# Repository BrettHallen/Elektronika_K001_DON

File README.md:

# Электроника К 001 ДОН<br>Elektronika K 001 DON
Information about the Specialist-compatible constructor kit computer manufactured in Rostov-on-Don (Ростов-на-Дону) in the Russian SFSR by [ПАО "ГРАНИТ" (Granite)](https://www.paogranit.ru/) in the late 1980s.

Here is the packaging - the poly is quite dense and in very good condition, but the label has degraded somewhat I'm afraid.<br>

The blurb on the top of the box says the following:<br>
> Набор "Конструктор" Персональной микро-ЭВМ<br>
>
> Набор-конструктор микро-ЭВМ:<br>
> 1. Для сборки микро-ЭВМ;
> 2. Для ознакомления с устройством микро-ЭВМ;
> 3. Для ознакомления с основами компьютерной техники.<br>
>
> Собранная микро-ЭВМ:
> 1. Обучает по разным общеобразовательным и специальным программам;
> 2. Решает задачи в режиме программируемого калькулятора;
> 3. Реализует разнообразные программы интеллектуальных игр;
> 4. Хранит составленный Вами банк данных.

In English:<br>
> Kit "Constructor" Personal Microcomputer<br>
>
> Microcomputer Constructor Kit:<br>
> 1. For assembling a microcomputer;
> 2. For familiarising yourself with the structure of a microcomputer;
> 3. For familiarising yourself with the basics of computer technology.
>
> Assembled microcomputer:
> 1. Provides training using various general education and specialised programs;
> 2. Solves problems in programmable calculator mode;
> 3. Runs a variety of intellectual game programs;
> 4. Stores the database you have created.

## Videos
- [Part 1: Initial Look](https://youtu.be/PEJ6cLXKCgM)
- [Part 2: First Power On](https://youtu.be/MBkoUaQZSSI)
- [Part 3: Video Fault](https://youtu.be/eovsz4YsJxw)

## Firmware
A dump of the КС573РФ2 (2716 analogue) EPROM.<br>

This has some minor differences with the original C000 Loader binary for the [Specialist](/Specialist_Information/Firmware).<br>

## Video Output
It has a 5-pin DIN for audio & video output:<br>
- Pin 1 = audio
- Pin 2 = ground
- Pin 3 = n/c
- Pin 4 = video (B&W)
- Pin 5 = n/c

## [Power](/Elektronika_K001_DON_Power)
This appears to be the pinout for the 5-pin DIN power socket:
- Pin 1 = +12V regulated
- Pin 2 = ground (общий)
- Pin 3 = +5V regulated
- Pin 4 = -5V unregulated
- Pin 5 = -5V unregulated

I have created a simple replacement that uses a regulated +12VDC power supply and generates regulated ±5V output.<br>

## [Replacement Keyboard](/Elektronika_K001_DON_Keyboard)
The keyboard is a pretty neat design for the time, nice & simple.  Luckily it is quite easy to replace so here is my attempt using Cherry MX key switches.<br>

Interestingly the Specialist design has a row of function keys along the top: HELP, EDIT, RUN, etc.<br>

These aren't labelled on the K001 DON but they should function - I have included them.<br>

### Special Keys
There are some Soviet-specific keys on the keyboard - here is my rough understanding:
- НР = Нижний Регистр (lower case/register)
- НР ФИКС = Нижний Регистр Fix (shift lock)
- ЗБ = Забой (backspace)
- ПС = Перевод Строки (line feed)
- ПВ = Повтор/Вставка (auto-repeat)
- ВК = Возврат Каретки (carriage return)
- СБР = Сброс (reset)

## Useful Links
### [Alexey's Vintage Sovit Computer Repository](/Specialist_Information)
A great source of information about the Specialist design can be found on [Alexey's retro computer repository](https://github.com/alemorf/retro_computers).<br>

I have copied some of the useful information such as the original firmware and "Modelist Constructor" magazine articles.<br>

### [Mick Laboratory](http://www.micklab.ru/Specialist.htm)

### [spetsialist-mx.ru](https://web.archive.org/web/20210722200656/http://www.spetsialist-mx.ru/)
Unfortunately the original site is lost so there is only this archive.  I have added some of the useful info to the Specialist section here as an additional backup - this included a [scan of the DON's manual](https://web.archive.org/web/20210516222216/http://spetsialist-mx.ru/index16.html)!

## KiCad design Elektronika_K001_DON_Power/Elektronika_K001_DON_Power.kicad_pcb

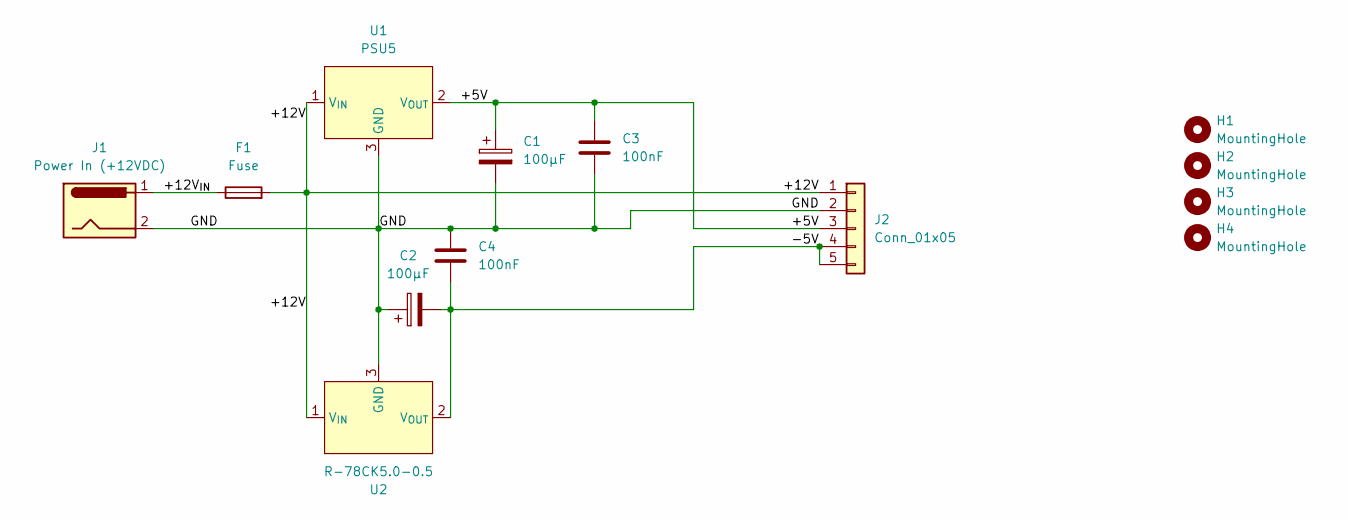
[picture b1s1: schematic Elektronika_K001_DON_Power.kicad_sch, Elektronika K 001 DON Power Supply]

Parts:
C1, C2: 100µF; CP_Radial_D6.3mm_P2.50mm
C3, C4: 100nF; C_Disc_D3.8mm_W2.6mm_P2.50mm
F1: Fuse; Fuseholder_Clip-5x20mm_Littelfuse_111_Inline_P20.00x5.00mm_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
H1, H2, H3, H4: MountingHole; MountingHole_3.2mm_M3_DIN965
J1: Power In (+12VDC); BarrelJack_CUI_PJ-063AH_Horizontal
J2: Conn_01x05; 6710601
U1: PSU5; TO-3
U2: R-78CK5.0-0.5; TO-220-3_Vertical; Manufacturer_Part_Number R-78CK5.0-0.5

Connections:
/+5V: C1.1, C3.1, J2.3, U1.2 (V_{OUT})
/+12V: F1.2, J2.1, U1.1 (V_{IN}), U2.1 (V_{IN})
/+12V_{IN}: F1.1, J1.1
/-5V: C2.2, C4.1, J2.4, J2.5, U2.2 (V_{OUT})
/GND: C1.2, C2.1, C3.2, C4.2, J1.2, J2.2, U1.3 (GND), U2.3 (GND)

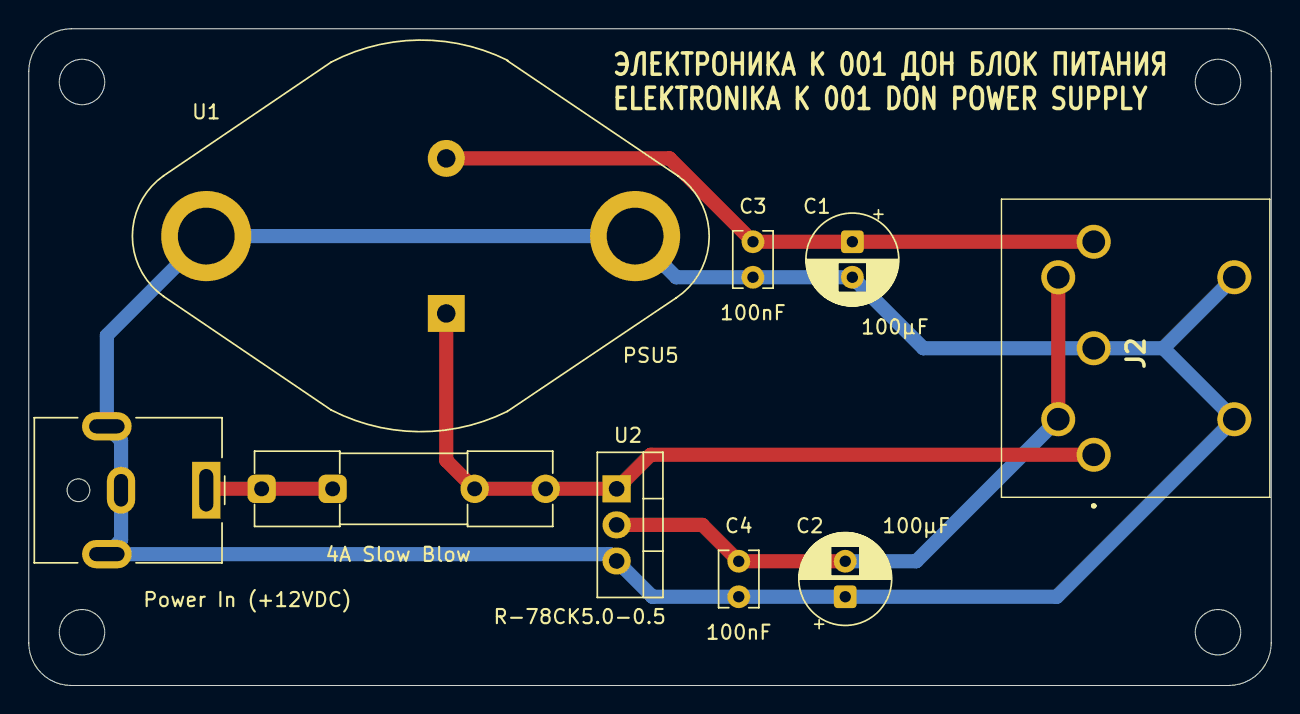
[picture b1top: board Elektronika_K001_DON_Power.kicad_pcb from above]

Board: 2 copper layers, 87.5 x 46.2 mm, 13 parts (0 on the bottom side), 5 nets.

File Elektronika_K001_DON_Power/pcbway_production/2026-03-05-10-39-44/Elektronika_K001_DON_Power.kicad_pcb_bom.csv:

Designator,Quantity,Value,Footprint,Package,MPN,DNP,Mount_Type,Description,Height,Manufacturer_Name
"C1, C2",2,100µF,CP_Radial_D6.3mm_P2.50mm,,,,tht,Polarized capacitor,,
"C3, C4",2,100nF,C_Disc_D3.8mm_W2.6mm_P2.50mm,,,,tht,Unpolarized capacitor,,
J1,1,Power In (+12VDC),BarrelJack_CUI_PJ-063AH_Horizontal,,,,tht,DC Barrel Jack,,
J2,1,Conn_01x05,6710601,,,,tht,"Generic connector, single row, 01x05, script generated (kicad-library-utils/schlib/autogen/connector/)",,
U1,1,PSU5,TO-3,,,,tht,,,
U2,1,R-78CK5.0-0.5,TO-220-3_Vertical,,R-78CK5.0-0.5,,tht,0.5A DC/DC-Converter \'INNOLINE\' SIP3 reg,10.7,RECOM Power

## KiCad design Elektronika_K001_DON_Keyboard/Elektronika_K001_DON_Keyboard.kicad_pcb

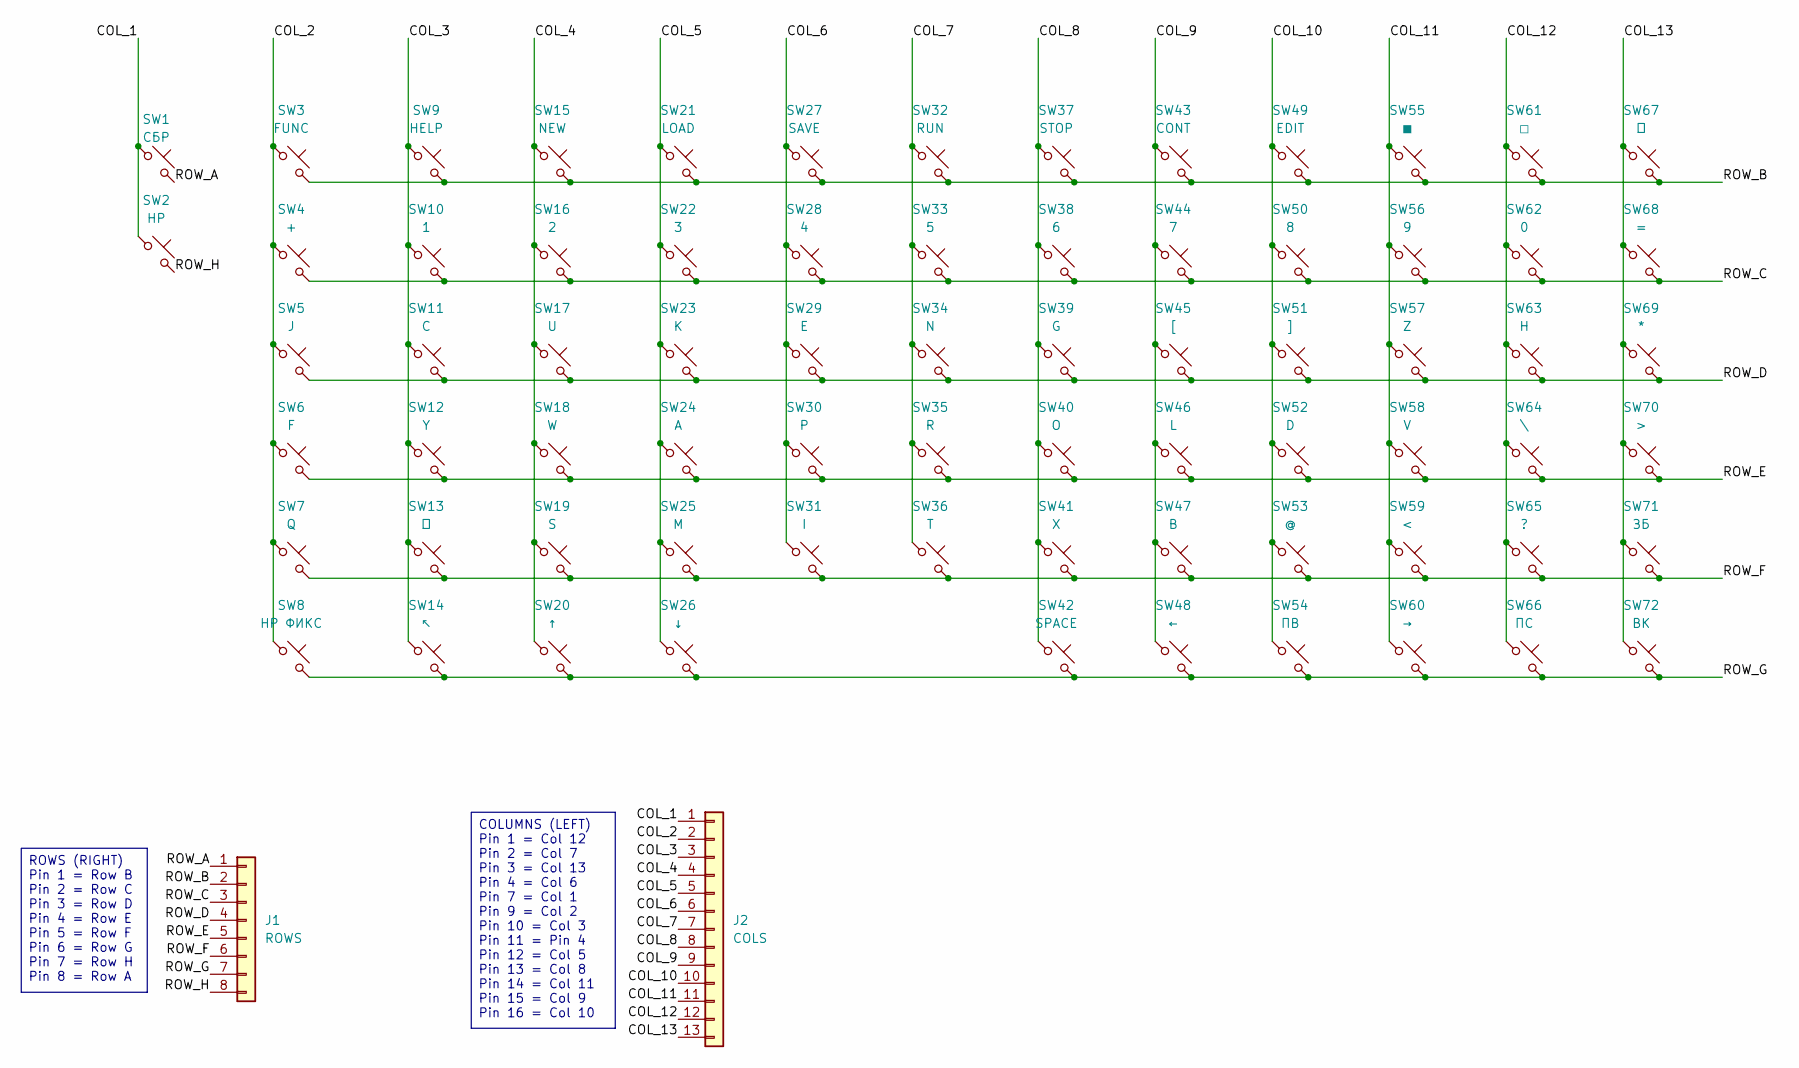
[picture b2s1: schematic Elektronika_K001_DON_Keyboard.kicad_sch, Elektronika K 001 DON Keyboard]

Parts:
J1: ROWS; PinHeader_1x08_P2.54mm_Vertical
J2: COLS; PinHeader_1x13_P2.54mm_Vertical
SW1: СБР; SW_Gateron_LowProfile_THT
SW2: НР; SW_Gateron_LowProfile_THT
SW3: FUNC; SW_Gateron_LowProfile_THT
SW4: +; SW_Gateron_LowProfile_THT
SW5: J; SW_Gateron_LowProfile_THT
SW6: F; SW_Gateron_LowProfile_THT
SW7: Q; SW_Gateron_LowProfile_THT
SW8: НР ФИКС; SW_Gateron_LowProfile_THT
SW9: HELP; SW_Gateron_LowProfile_THT
SW10: 1; SW_Gateron_LowProfile_THT
SW11: C; SW_Gateron_LowProfile_THT
SW12: Y; SW_Gateron_LowProfile_THT
SW13: ⎴; SW_Gateron_LowProfile_THT
SW14: ↖; SW_Gateron_LowProfile_THT
SW15: NEW; SW_Gateron_LowProfile_THT
SW16: 2; SW_Gateron_LowProfile_THT
SW17: U; SW_Gateron_LowProfile_THT
SW18: W; SW_Gateron_LowProfile_THT
SW19: S; SW_Gateron_LowProfile_THT
SW20: ↑; SW_Gateron_LowProfile_THT
SW21: LOAD; SW_Gateron_LowProfile_THT
SW22: 3; SW_Gateron_LowProfile_THT
SW23: K; SW_Gateron_LowProfile_THT
SW24: A; SW_Gateron_LowProfile_THT
SW25: M; SW_Gateron_LowProfile_THT
SW26: ↓; SW_Gateron_LowProfile_THT
SW27: SAVE; SW_Gateron_LowProfile_THT
SW28: 4; SW_Gateron_LowProfile_THT
SW29: E; SW_Gateron_LowProfile_THT
SW30: P; SW_Gateron_LowProfile_THT
SW31: I; SW_Gateron_LowProfile_THT
SW32: RUN; SW_Gateron_LowProfile_THT
SW33: 5; SW_Gateron_LowProfile_THT
SW34: N; SW_Gateron_LowProfile_THT
SW35: R; SW_Gateron_LowProfile_THT
SW36: T; SW_Gateron_LowProfile_THT
SW37: STOP; SW_Gateron_LowProfile_THT
SW38: 6; SW_Gateron_LowProfile_THT
SW39: G; SW_Gateron_LowProfile_THT
SW40: O; SW_Gateron_LowProfile_THT
SW41: X; SW_Gateron_LowProfile_THT
SW42: SPACE; SW_Gateron_LowProfile_THT
SW43: CONT; SW_Gateron_LowProfile_THT
SW44: 7; SW_Gateron_LowProfile_THT
SW45: [; SW_Gateron_LowProfile_THT
SW46: L; SW_Gateron_LowProfile_THT
SW47: B; SW_Gateron_LowProfile_THT
SW48: ←; SW_Gateron_LowProfile_THT
SW49: EDIT; SW_Gateron_LowProfile_THT
SW50: 8; SW_Gateron_LowProfile_THT
SW51: ]; SW_Gateron_LowProfile_THT
SW52: D; SW_Gateron_LowProfile_THT
SW53: @; SW_Gateron_LowProfile_THT
SW54: ПВ; SW_Gateron_LowProfile_THT
SW55: ◼; SW_Gateron_LowProfile_THT
SW56: 9; SW_Gateron_LowProfile_THT
SW57: Z; SW_Gateron_LowProfile_THT
SW58: V; SW_Gateron_LowProfile_THT
SW59: <; SW_Gateron_LowProfile_THT
SW60: →; SW_Gateron_LowProfile_THT
SW61: ◻; SW_Gateron_LowProfile_THT
SW62: 0; SW_Gateron_LowProfile_THT
SW63: H; SW_Gateron_LowProfile_THT
SW64: \; SW_Gateron_LowProfile_THT
SW65: ?; SW_Gateron_LowProfile_THT
SW66: ПС; SW_Gateron_LowProfile_THT
SW67: ⎅; SW_Gateron_LowProfile_THT
SW68: =; SW_Gateron_LowProfile_THT
SW69: *; SW_Gateron_LowProfile_THT
SW70: >; SW_Gateron_LowProfile_THT
SW71: ЗБ; SW_Gateron_LowProfile_THT
SW72: ВК; SW_Gateron_LowProfile_THT

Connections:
/COL_1: J2.1, SW1.1, SW2.1
/COL_2: J2.2, SW3.1, SW4.1, SW5.1, SW6.1, SW7.1, SW8.1
/COL_3: J2.3, SW9.1, SW10.1, SW11.1, SW12.1, SW13.1, SW14.1
/COL_4: J2.4, SW15.1, SW16.1, SW17.1, SW18.1, SW19.1, SW20.1
/COL_5: J2.5, SW21.1, SW22.1, SW23.1, SW24.1, SW25.1, SW26.1
/COL_6: J2.6, SW27.1, SW28.1, SW29.1, SW30.1, SW31.1
/COL_7: J2.7, SW32.1, SW33.1, SW34.1, SW35.1, SW36.1
/COL_8: J2.8, SW37.1, SW38.1, SW39.1, SW40.1, SW41.1, SW42.1
/COL_9: J2.9, SW43.1, SW44.1, SW45.1, SW46.1, SW47.1, SW48.1
/COL_10: J2.10, SW49.1, SW50.1, SW51.1, SW52.1, SW53.1, SW54.1
/COL_11: J2.11, SW55.1, SW56.1, SW57.1, SW58.1, SW59.1, SW60.1
/COL_12: J2.12, SW61.1, SW62.1, SW63.1, SW64.1, SW65.1, SW66.1
/COL_13: J2.13, SW67.1, SW68.1, SW69.1, SW70.1, SW71.1, SW72.1
/ROW_A: J1.1, SW1.2
/ROW_B: J1.2, SW3.2, SW9.2, SW15.2, SW21.2, SW27.2, SW32.2, SW37.2, SW43.2, SW49.2, SW55.2, SW61.2, SW67.2
/ROW_C: J1.3, SW4.2, SW10.2, SW16.2, SW22.2, SW28.2, SW33.2, SW38.2, SW44.2, SW50.2, SW56.2, SW62.2, SW68.2
/ROW_D: J1.4, SW5.2, SW11.2, SW17.2, SW23.2, SW29.2, SW34.2, SW39.2, SW45.2, SW51.2, SW57.2, SW63.2, SW69.2
/ROW_E: J1.5, SW6.2, SW12.2, SW18.2, SW24.2, SW30.2, SW35.2, SW40.2, SW46.2, SW52.2, SW58.2, SW64.2, SW70.2
/ROW_F: J1.6, SW7.2, SW13.2, SW19.2, SW25.2, SW31.2, SW36.2, SW41.2, SW47.2, SW53.2, SW59.2, SW65.2, SW71.2
/ROW_G: J1.7, SW8.2, SW14.2, SW20.2, SW26.2, SW42.2, SW48.2, SW54.2, SW60.2, SW66.2, SW72.2
/ROW_H: J1.8, SW2.2

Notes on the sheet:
COLUMNS (LEFT) Pin 1 = Col 12 Pin 2 = Col 7 Pin 3 = Col 13 Pin 4 = Col 6 Pin 7 = Col 1 Pin 9 = Col 2 Pin 10 = Col 3 Pin 11 = Pin 4 Pin 12 = Col 5 Pin 13 = Col 8 Pin 14 = Col 11 Pin 15 = Col 9 Pin 16 = Col 10
ROWS (RIGHT) Pin 1 = Row B Pin 2 = Row C Pin 3 = Row D Pin 4 = Row E Pin 5 = Row F Pin 6 = Row G Pin 7 = Row H Pin 8 = Row A

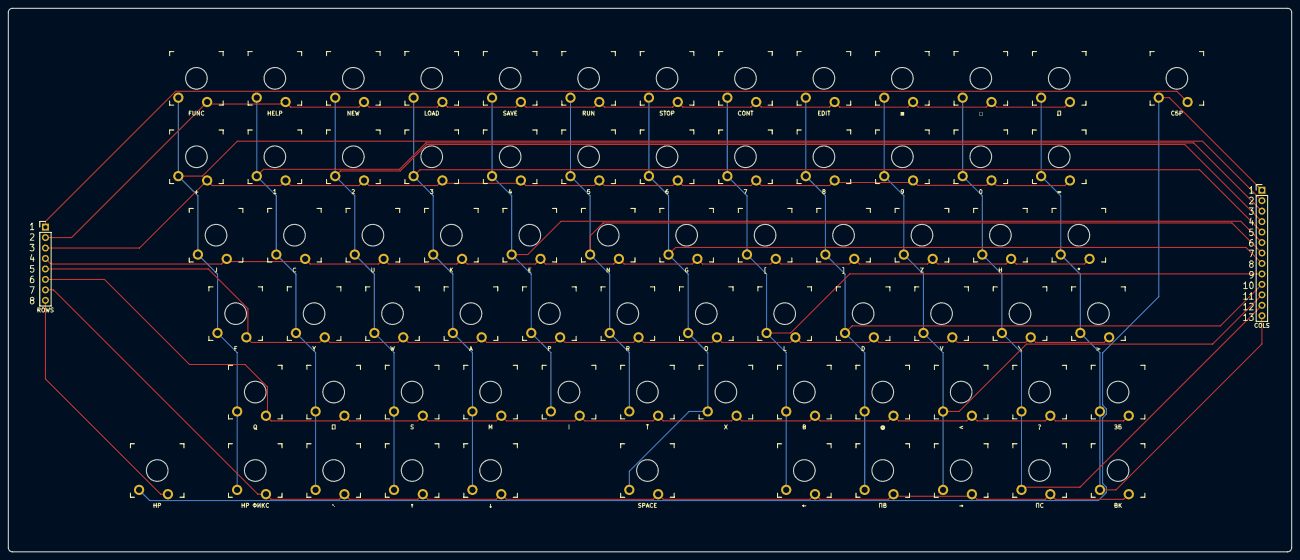
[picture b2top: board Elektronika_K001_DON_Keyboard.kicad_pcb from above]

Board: 2 copper layers, 311.7 x 132.0 mm, 74 parts (0 on the bottom side), 21 nets.

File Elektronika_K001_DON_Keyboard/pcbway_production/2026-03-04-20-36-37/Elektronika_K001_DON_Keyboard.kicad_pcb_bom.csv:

Designator,Quantity,Value,Footprint,Package,MPN,DNP,Mount_Type,Description
J1,1,ROWS,PinHeader_1x08_P2.54mm_Vertical,,,,tht,"Generic connector, single row, 01x08, script generated (kicad-library-utils/schlib/autogen/connector/)"
J2,1,COLS,PinHeader_1x13_P2.54mm_Vertical,,,,tht,"Generic connector, single row, 01x13, script generated (kicad-library-utils/schlib/autogen/connector/)"
SW1,1,СБР,SW_Cherry_MX_PCB_1.00u,,,,tht,"Push button switch, normally open, two pins, 45° tilted"
SW10,1,1,SW_Cherry_MX_PCB_1.00u,,,,tht,"Push button switch, normally open, two pins, 45° tilted"
SW11,1,C,SW_Cherry_MX_PCB_1.00u,,,,tht,"Push button switch, normally open, two pins, 45° tilted"
SW12,1,Y,SW_Cherry_MX_PCB_1.00u,,,,tht,"Push button switch, normally open, two pins, 45° tilted"
SW13,1,⎴,SW_Cherry_MX_PCB_1.00u,,,,tht,"Push button switch, normally open, two pins, 45° tilted"
SW14,1,↖,SW_Cherry_MX_PCB_1.00u,,,,tht,"Push button switch, normally open, two pins, 45° tilted"
SW15,1,NEW,SW_Cherry_MX_PCB_1.00u,,,,tht,"Push button switch, normally open, two pins, 45° tilted"
SW16,1,2,SW_Cherry_MX_PCB_1.00u,,,,tht,"Push button switch, normally open, two pins, 45° tilted"
SW17,1,U,SW_Cherry_MX_PCB_1.00u,,,,tht,"Push button switch, normally open, two pins, 45° tilted"
SW18,1,W,SW_Cherry_MX_PCB_1.00u,,,,tht,"Push button switch, normally open, two pins, 45° tilted"
SW19,1,S,SW_Cherry_MX_PCB_1.00u,,,,tht,"Push button switch, normally open, two pins, 45° tilted"
SW2,1,НР,SW_Cherry_MX_PCB_1.00u,,,,tht,"Push button switch, normally open, two pins, 45° tilted"
SW20,1,↑,SW_Cherry_MX_PCB_1.00u,,,,tht,"Push button switch, normally open, two pins, 45° tilted"
SW21,1,LOAD,SW_Cherry_MX_PCB_1.00u,,,,tht,"Push button switch, normally open, two pins, 45° tilted"
SW22,1,3,SW_Cherry_MX_PCB_1.00u,,,,tht,"Push button switch, normally open, two pins, 45° tilted"
SW23,1,K,SW_Cherry_MX_PCB_1.00u,,,,tht,"Push button switch, normally open, two pins, 45° tilted"
SW24,1,A,SW_Cherry_MX_PCB_1.00u,,,,tht,"Push button switch, normally open, two pins, 45° tilted"
SW25,1,M,SW_Cherry_MX_PCB_1.00u,,,,tht,"Push button switch, normally open, two pins, 45° tilted"
SW26,1,↓,SW_Cherry_MX_PCB_1.00u,,,,tht,"Push button switch, normally open, two pins, 45° tilted"
SW27,1,SAVE,SW_Cherry_MX_PCB_1.00u,,,,tht,"Push button switch, normally open, two pins, 45° tilted"
SW28,1,4,SW_Cherry_MX_PCB_1.00u,,,,tht,"Push button switch, normally open, two pins, 45° tilted"
SW29,1,E,SW_Cherry_MX_PCB_1.00u,,,,tht,"Push button switch, normally open, two pins, 45° tilted"
SW3,1,FUNC,SW_Cherry_MX_PCB_1.00u,,,,tht,"Push button switch, normally open, two pins, 45° tilted"
SW30,1,P,SW_Cherry_MX_PCB_1.00u,,,,tht,"Push button switch, normally open, two pins, 45° tilted"
SW31,1,I,SW_Cherry_MX_PCB_1.00u,,,,tht,"Push button switch, normally open, two pins, 45° tilted"
SW32,1,RUN,SW_Cherry_MX_PCB_1.00u,,,,tht,"Push button switch, normally open, two pins, 45° tilted"
SW33,1,5,SW_Cherry_MX_PCB_1.00u,,,,tht,"Push button switch, normally open, two pins, 45° tilted"
SW34,1,N,SW_Cherry_MX_PCB_1.00u,,,,tht,"Push button switch, normally open, two pins, 45° tilted"
SW35,1,R,SW_Cherry_MX_PCB_1.00u,,,,tht,"Push button switch, normally open, two pins, 45° tilted"
SW36,1,T,SW_Cherry_MX_PCB_1.00u,,,,tht,"Push button switch, normally open, two pins, 45° tilted"
SW37,1,STOP,SW_Cherry_MX_PCB_1.00u,,,,tht,"Push button switch, normally open, two pins, 45° tilted"
SW38,1,6,SW_Cherry_MX_PCB_1.00u,,,,tht,"Push button switch, normally open, two pins, 45° tilted"
SW39,1,G,SW_Cherry_MX_PCB_1.00u,,,,tht,"Push button switch, normally open, two pins, 45° tilted"
SW4,1,+,SW_Cherry_MX_PCB_1.00u,,,,tht,"Push button switch, normally open, two pins, 45° tilted"
SW40,1,O,SW_Cherry_MX_PCB_1.00u,,,,tht,"Push button switch, normally open, two pins, 45° tilted"
SW41,1,X,SW_Cherry_MX_PCB_1.00u,,,,tht,"Push button switch, normally open, two pins, 45° tilted"
SW42,1,SPACE,SW_Cherry_MX_PCB_1.00u,,,,tht,"Push button switch, normally open, two pins, 45° tilted"
SW43,1,CONT,SW_Cherry_MX_PCB_1.00u,,,,tht,"Push button switch, normally open, two pins, 45° tilted"
SW44,1,7,SW_Cherry_MX_PCB_1.00u,,,,tht,"Push button switch, normally open, two pins, 45° tilted"
SW45,1,[,SW_Cherry_MX_PCB_1.00u,,,,tht,"Push button switch, normally open, two pins, 45° tilted"
SW46,1,L,SW_Cherry_MX_PCB_1.00u,,,,tht,"Push button switch, normally open, two pins, 45° tilted"
SW47,1,B,SW_Cherry_MX_PCB_1.00u,,,,tht,"Push button switch, normally open, two pins, 45° tilted"
SW48,1,←,SW_Cherry_MX_PCB_1.00u,,,,tht,"Push button switch, normally open, two pins, 45° tilted"
SW49,1,EDIT,SW_Cherry_MX_PCB_1.00u,,,,tht,"Push button switch, normally open, two pins, 45° tilted"
SW5,1,J,SW_Cherry_MX_PCB_1.00u,,,,tht,"Push button switch, normally open, two pins, 45° tilted"
SW50,1,8,SW_Cherry_MX_PCB_1.00u,,,,tht,"Push button switch, normally open, two pins, 45° tilted"
SW51,1,],SW_Cherry_MX_PCB_1.00u,,,,tht,"Push button switch, normally open, two pins, 45° tilted"
SW52,1,D,SW_Cherry_MX_PCB_1.00u,,,,tht,"Push button switch, normally open, two pins, 45° tilted"
SW53,1,@,SW_Cherry_MX_PCB_1.00u,,,,tht,"Push button switch, normally open, two pins, 45° tilted"
SW54,1,ПВ,SW_Cherry_MX_PCB_1.00u,,,,tht,"Push button switch, normally open, two pins, 45° tilted"
SW55,1,◼,SW_Cherry_MX_PCB_1.00u,,,,tht,"Push button switch, normally open, two pins, 45° tilted"
SW56,1,9,SW_Cherry_MX_PCB_1.00u,,,,tht,"Push button switch, normally open, two pins, 45° tilted"
SW57,1,Z,SW_Cherry_MX_PCB_1.00u,,,,tht,"Push button switch, normally open, two pins, 45° tilted"
SW58,1,V,SW_Cherry_MX_PCB_1.00u,,,,tht,"Push button switch, normally open, two pins, 45° tilted"
SW59,1,<,SW_Cherry_MX_PCB_1.00u,,,,tht,"Push button switch, normally open, two pins, 45° tilted"
SW6,1,F,SW_Cherry_MX_PCB_1.00u,,,,tht,"Push button switch, normally open, two pins, 45° tilted"
SW60,1,→,SW_Cherry_MX_PCB_1.00u,,,,tht,"Push button switch, normally open, two pins, 45° tilted"
SW61,1,◻,SW_Cherry_MX_PCB_1.00u,,,,tht,"Push button switch, normally open, two pins, 45° tilted"
SW62,1,0,SW_Cherry_MX_PCB_1.00u,,,,tht,"Push button switch, normally open, two pins, 45° tilted"
SW63,1,H,SW_Cherry_MX_PCB_1.00u,,,,tht,"Push button switch, normally open, two pins, 45° tilted"
SW64,1,\,SW_Cherry_MX_PCB_1.00u,,,,tht,"Push button switch, normally open, two pins, 45° tilted"
SW65,1,?,SW_Cherry_MX_PCB_1.00u,,,,tht,"Push button switch, normally open, two pins, 45° tilted"
SW66,1,ПС,SW_Cherry_MX_PCB_1.00u,,,,tht,"Push button switch, normally open, two pins, 45° tilted"
SW67,1,⎅,SW_Cherry_MX_PCB_1.00u,,,,tht,"Push button switch, normally open, two pins, 45° tilted"
SW68,1,=,SW_Cherry_MX_PCB_1.00u,,,,tht,"Push button switch, normally open, two pins, 45° tilted"
SW69,1,*,SW_Cherry_MX_PCB_1.00u,,,,tht,"Push button switch, normally open, two pins, 45° tilted"
SW7,1,Q,SW_Cherry_MX_PCB_1.00u,,,,tht,"Push button switch, normally open, two pins, 45° tilted"
SW70,1,>,SW_Cherry_MX_PCB_1.00u,,,,tht,"Push button switch, normally open, two pins, 45° tilted"
SW71,1,ЗБ,SW_Cherry_MX_PCB_1.00u,,,,tht,"Push button switch, normally open, two pins, 45° tilted"
SW72,1,ВК,SW_Cherry_MX_PCB_1.00u,,,,tht,"Push button switch, normally open, two pins, 45° tilted"
SW8,1,НР ФИКС,SW_Cherry_MX_PCB_1.00u,,,,tht,"Push button switch, normally open, two pins, 45° tilted"
SW9,1,HELP,SW_Cherry_MX_PCB_1.00u,,,,tht,"Push button switch, normally open, two pins, 45° tilted"

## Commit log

2026-03-04 Finalised design for testing
2026-03-04 Added magazine articles as PDF
2026-03-04 From Alexy's repository
2026-03-04 From Alexey's repository
2026-03-05 Added PCB images
2026-03-05 Black background
2026-03-05 Added keyboard pictures
2026-03-06 Added keyboard connector pinouts
2026-03-08 Replaced Cherry MX with Gateron LP
2026-03-14 Added fuse on 12V input
